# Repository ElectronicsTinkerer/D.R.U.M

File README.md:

# D.R.U.M (Digital Rhythmic Utility Modules)
Files for the D.R.U.M. Machine, the modular, expandable drum machine complete with digital AND analog circuitry!

## File Structure

```
.
├── doc             # Documentation on components, thoughts, h/sware details
├── module          # Files specific to the modules
│   ├── cad         # Housing design
│   ├── hardware    # PCB design (kicad)
│   └── software    # Module firmware
├── README.md       # INFO (this doc)
├── samples         # Sample to c-array conversion utils
│   └── bass-0      # Revision 0 Bass Drum samples (RAW, PCM-16)
├── sequencer       # Files specific to the sequencer
│   ├── cad         # Housing design
│   ├── hardware    # PCB design (kicad)
│   └── software    # Sequencer firmware
└── slidepot        # Slide potentiometer daughter board
    ├── cad         # 3D models for slidepot (knob)
    └── hardware    # Daughter board design
```

## System Architecture

The D.R.U.M. system is composed of a sequencer (the base and primary controller) and between 1 and 8 "modules." The digital section of each device is based on the RP2040 microcontroller, the same device found on the Raspberry Pi Pico development board. The RP2040 was selected due to its relatively high clock speed (compared to a '328, for example), multiple cores, its PIO state machines, good documentation, and great SDK. (Oh, and it's only $1). 

The **analog section** is designed around a completely passive routing scheme, where each of the channels is simply shifted one position over each module. This allows for up to 8 modules to be connected in series before a summing module is necessary to combine the channels. Each module has a 100k pull down resistor on the lines to ensure that they are not floating. The eight lines enter the sequencer for final summation and are dc isolated via separate capacitors for each line. Although currently unused, each module also has a comparator circuit on channel 8 to detect when all the channels have been filled to signal to the RP2040 onboard that the max channel count has been reached. Each module is in charge of the amplitude that it outputs; that is, the mixing between each module is performed on a per-module basis.

The **digital section** is designed around the RP2040 microcontroller. All the modules communicate over a 32-bit SPI-like scan chain which is controlled by the sequencer. The scan chain is further documented below. The modules have the ability to send an interrupt to the sequencer when they have been "(un)selected" by the user. Only one device can be "selected" at a time. Being selected means that that module's data will be copied to the sequencer and displayed on the UI. Deselection of the module hides this information from the user but retains it within the module's memory, allowing multiple modules to have different user data. Tempo synchronization between the modules is accomplished by an interrupt line which is driven by the sequencer. This outputs a periodic pulse each "tick" (currently each beat, but in the future when microbeats are implemented, this will pulse each microbeat). The length of the tick tells the module if the beat is the start of a new measure. A short pulse (<75us) is beat 0 while a long pulse (>75us) is any other beat.

The overall routing of signals is approximated by the following diagram:

## Docs

The `doc` directory contains most of the relevant documentation to this project. This will contain information about different parts of the system, such as the serial bus protocol or the data sheets for the components used.

* [`serbus.md`](doc/serbus.md) contains information on the custom 32-bit scan chain protocol used for communication between modules. This is implemented using the RP2040's PIO state machines, meaning that the bus can be much faster than bit-banging in software. It also allows an "address-free" control scheme, where modules (bus devices) are selected by their depth on the scan chain, rather than an address. This allows a user to completely fill the bus with 8 of the same module if desired.
* [`ipc.md`](doc/ipc.md) contains information on how information is sent between the different processes running on the sequencer and the module. Both CPU cores on the RP2040 are utilized in each design to allow simultaneous execution of multiple tasks. In the case of the sequencer, the I2C bus is rather slow compared to the amount of data to be sent over it, so the second thread (core 1) handles data modification and transfer to/from the modules.
* [`samples.md`](doc/samples.md) contains information on the used sample format and how playback is achieved as well as how the signed to unsigned conversion is performed.

## Usage

### Power Up / Reset

Upon power up, the sequencer will run through an auto detection routine to determine how many modules are connected. It also will cycle all neo pixels in the 4x4 grid pad white to visually test that all LEDs and their individual colors are functioning properly. After this initialization sequence is performed, the sequencer will display its default config on the OLED screen.

### Programming a Beat

To start programming in a beat, the user must first select the module that they would like to program. Modules should have a button on board along with a visual indicator which can be used to select/deselect a module and identify if a module is selected. When a module is selected, the current contents of the sequencer's beat grid are saved to the previously selected module and the newly selected module's saved beat data is loaded into the grid.

Each square on the grid represents a sixteenth note (1/16) at the current tempo marking (although this may be changed in future revisions). Additionally, each square can have up to 7 different values associated with it. These values are called the *velocity* of that note. In addition to the 7 different velocities, a square can be off, giving 8 total possible states. The state of all the squares is indicated by the color of that square. Additionally, each time that a square is pressed, its new velocity value is displayed on the OLED screen to give quantitative feedback on any changes. Beats can be programmed while the sequencer is in active playback or while the system is in a stopped state.

### Playback

Playback is controlled by the tempo knob. This knob controls the tempo by rotating it; clockwise increases the tempo by one beat per minute per click of the knob and counter-clockwise decreases the tempo. Pressing the know will switch the sequencer between active playback, *sequencing*, and stopped, *idle*, states. During playback, the current square will light up white to indicate the location of the beat. This light will extinguish during the idle state.

The time signature of the playback can be changed via the time signature knob. This cycles through all built-in time signatures in a circular manner. Beats which are not available in a given time signature will be "grayed out" with a dim white square. Note that beats which had been programmed before changing the time signature but are not available in a new time signature will retain their original values but will not be played back. Holding down the time signature knob for about one second will clear the current pattern on the grid.

### Interface

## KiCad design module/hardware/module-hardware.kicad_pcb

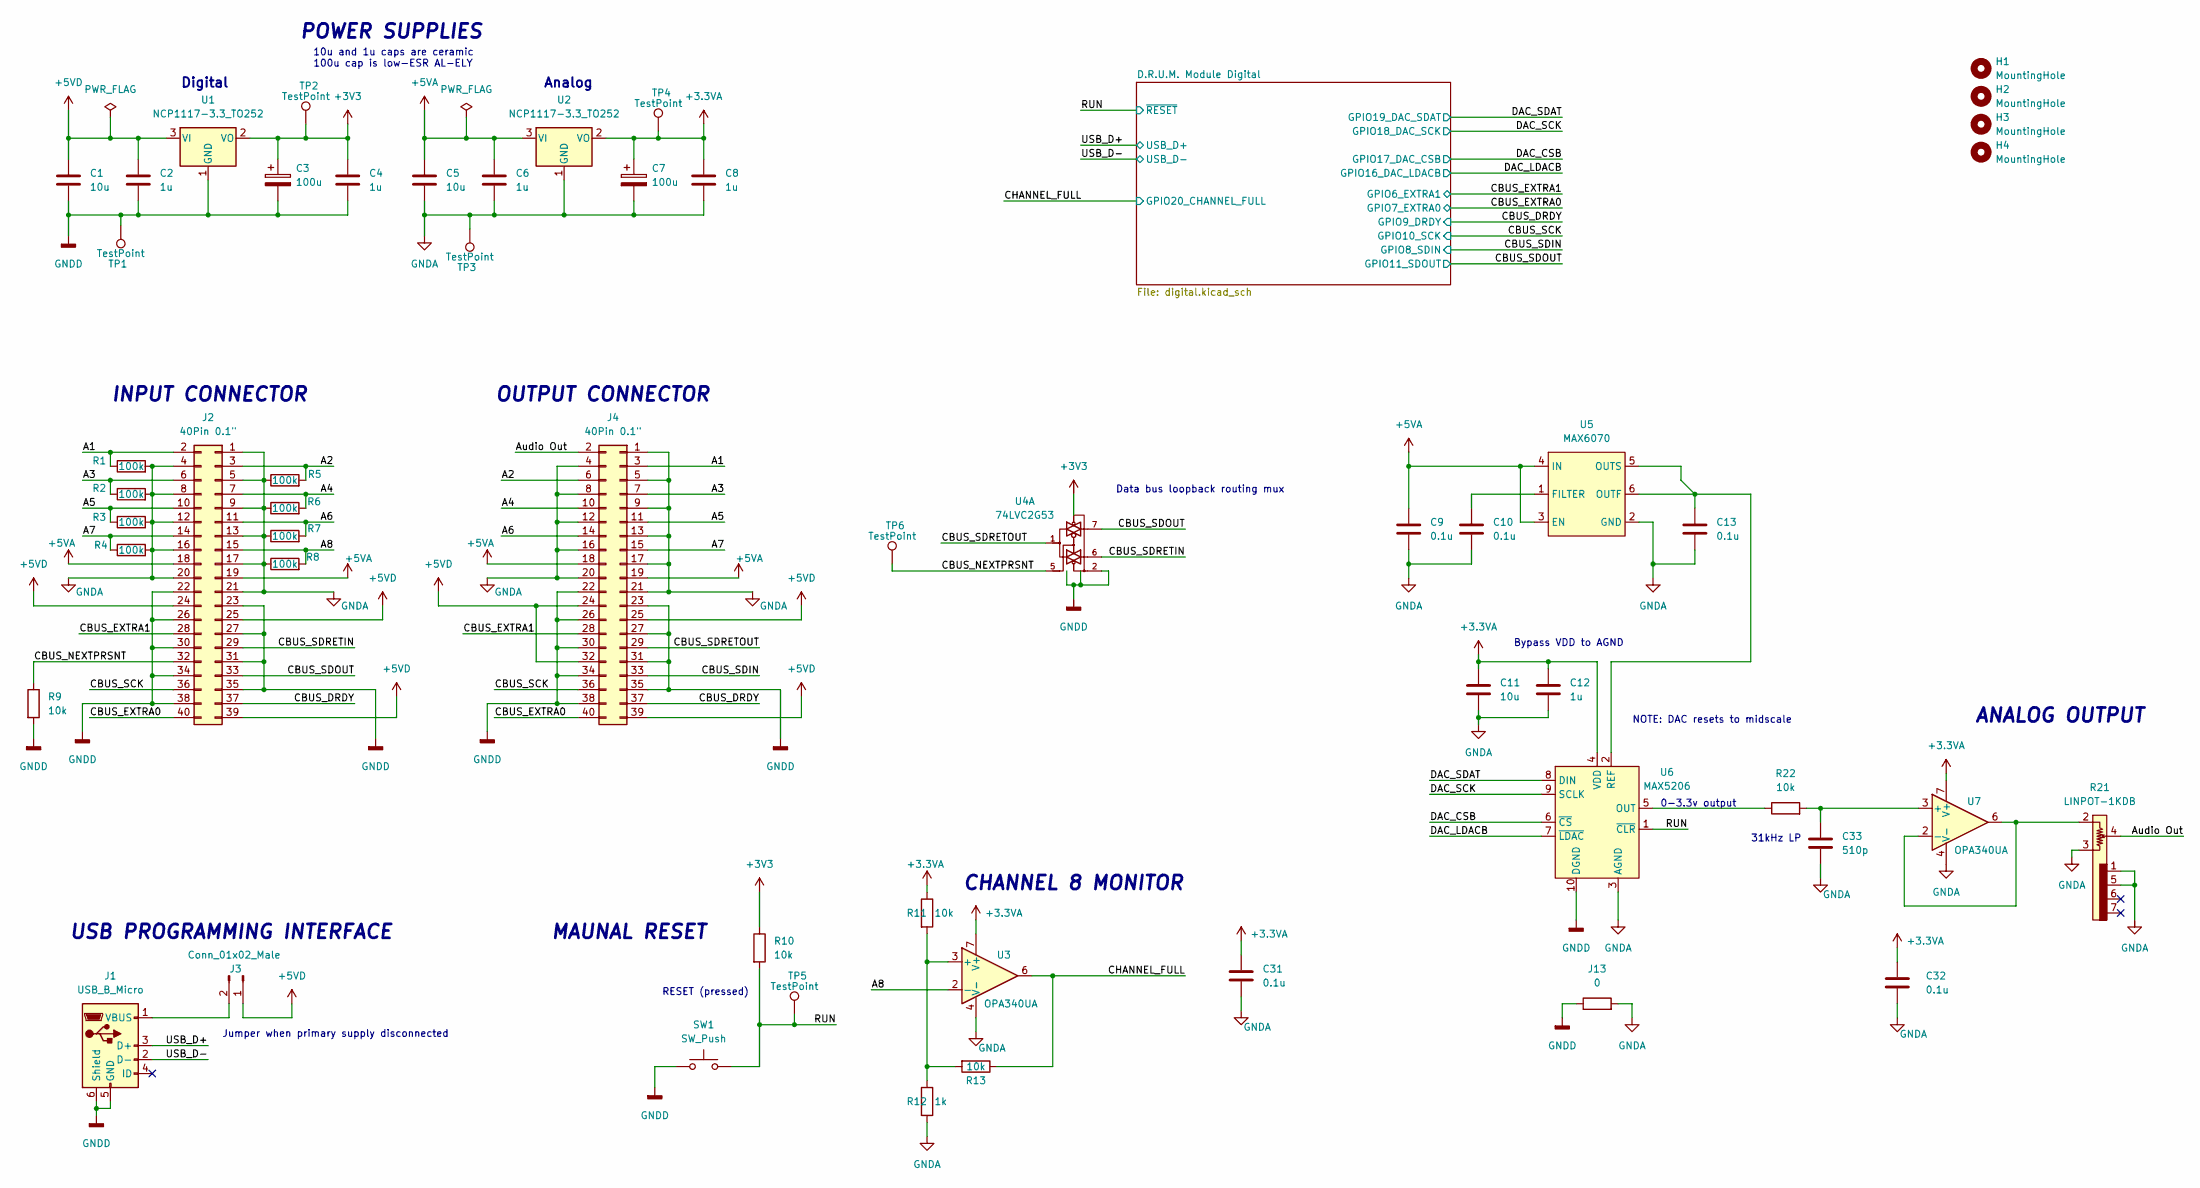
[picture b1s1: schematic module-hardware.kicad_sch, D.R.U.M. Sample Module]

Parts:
C1, C5, C11: 10u; C_1206_3216Metric_Pad1.33x1.80mm_HandSolder
C2, C4, C6, C8, C12: 1u; C_0603_1608Metric_Pad1.08x0.95mm_HandSolder
C3, C7: 100u; CP_Radial_D8.0mm_P3.50mm
C9, C10, C13, C31, C32: 0.1u; C_0603_1608Metric_Pad1.08x0.95mm_HandSolder
C33: 510p; C_0603_1608Metric_Pad1.08x0.95mm_HandSolder
H1, H2, H3, H4: MountingHole; MountingHole_3.2mm_M3
J1: USB_B_Micro; USB_Micro-B_Amphenol_10104110_Horizontal
J2: 40Pin 0.1"; PinHeader_2x20_P2.54mm_Horizontal
J3: Conn_01x02_Male; PinHeader_1x02_P2.54mm_Vertical
J4: 40Pin 0.1"; PinSocket_2x20_P2.54mm_Horizontal
J13: 0; SolderJumper-2_P1.3mm_Open_TrianglePad1.0x1.5mm
R1, R2, R3, R4, R5, R6, R7, R8: 100k; R_1206_3216Metric_Pad1.30x1.75mm_HandSolder
R9, R10, R11, R13, R22: 10k; R_0603_1608Metric_Pad0.98x0.95mm_HandSolder
R12: 1k; R_0603_1608Metric_Pad0.98x0.95mm_HandSolder
R21: LINPOT-1KDB; LINPOT-10KDB
SW1: SW_Push; TE_ConnMSLPT5252CG1
TP1, TP2, TP3, TP4, TP5, TP6: TestPoint; TestPoint_Pad_D1.5mm
U1, U2: NCP1117-3.3_TO252; TO-252-2
U3, U7: OPA340UA; SOIC-8_3.9x4.9mm_P1.27mm
U4: 74LVC2G53; VSSOP-8_2.3x2mm_P0.5mm
U5: MAX6070; SOT-23-6_Handsoldering
U6: MAX5206; MSOP-10_3x3mm_P0.5mm

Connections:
+3.3VA: C7.1, C8.1, C11.1, C12.1, C31.1, C32.1, R11.1, TP4.1, U2.2 (VO), U3.7 (V+), U6.4 (VDD), U7.7 (V+)
+3V3: C3.1, C4.1, R10.1, TP2.1, U1.2 (VO), U4.8 (VCC); also elsewhere on the board
+5VA: C5.1, C6.1, C9.1, J2.18, J2.19, J4.18, J4.19, U2.3 (VI), U5.3 (EN), U5.4 (IN)
+5VD: C1.1, C2.1, J2.24, J2.25, J2.39, J3.1, J4.24, J4.25, J4.32, J4.39, U1.3 (VI)
/A1: J2.2, J4.3, R1.1
/A2: J2.3, J4.6, R5.2
/A3: J2.6, J4.7, R2.1
/A4: J2.7, J4.10, R6.2
/A5: J2.10, J4.11, R3.1
/A6: J2.11, J4.14, R7.2
/A7: J2.14, J4.15, R4.1
/A8: J2.15, R8.2, U3.2 (-)
/Audio Out: J4.2, R21.4
/CBUS_DRDY: J2.37, J4.37; also elsewhere on the board
/CBUS_EXTRA0: J2.40, J4.40; also elsewhere on the board
/CBUS_EXTRA1: J2.28, J4.28; also elsewhere on the board
/CBUS_NEXTPRSNT: J2.32, R9.1, TP6.1, U4.5
/CBUS_SCK: J2.36, J4.36; also elsewhere on the board
/CBUS_SDIN: J4.33; also elsewhere on the board
/CBUS_SDOUT: J2.33, U4.7; also elsewhere on the board
/CBUS_SDRETIN: J2.29, U4.6
/CBUS_SDRETOUT: J4.29, U4.1
/CHANNEL_FULL: R13.1, U3.6; also elsewhere on the board
/DAC_CSB: U6.6 (~CS); also elsewhere on the board
/DAC_LDACB: U6.7 (~LDAC); also elsewhere on the board
/DAC_SCK: U6.9 (SCLK); also elsewhere on the board
/DAC_SDAT: U6.8 (DIN); also elsewhere on the board
/RUN: R10.2, SW1.2, TP5.1, U6.1 (~CLR); also elsewhere on the board
/USB_D+: J1.3 (D+); also elsewhere on the board
/USB_D-: J1.2 (D-); also elsewhere on the board
GND: C1.2, C2.2, C3.2, C4.2, J1.5 (GND), J1.6 (Shield), J2.22, J2.23, J2.26, J2.27, J2.30, J2.31, J2.34, J2.35, J2.38, J4.22, J4.23, J4.26, J4.27, J4.30, J4.31, J4.34, J4.35, J4.38, J13.1, R9.2, SW1.1, TP1.1, U1.1 (GND), U4.2, U4.3 (GND), U4.4 (GND), U6.10 (DGND); also elsewhere on the board
GNDA: C5.2, C6.2, C7.2, C8.2, C9.2, C10.2, C11.2, C12.2, C13.2, C31.2, C32.2, C33.2, J2.1, J2.4, J2.5, J2.8, J2.9, J2.12, J2.13, J2.16, J2.17, J2.20, J2.21, J4.1, J4.4, J4.5, J4.8, J4.9, J4.12, J4.13, J4.16, J4.17, J4.20, J4.21, J13.2, R1.2, R2.2, R3.2, R4.2, R5.1, R6.1, R7.1, R8.1, R12.2, R21.1, R21.3, R21.5, TP3.1, U2.1 (GND), U3.4 (V-), U5.2 (GND), U6.3 (AGND), U7.4 (V-)
unnamed: C10.1, U5.1 (FILTER)
unnamed: C13.1, U5.5 (OUTS), U5.6 (OUTF), U6.2 (REF)
unnamed: C33.1, R22.2, U7.3 (+)
unnamed: J1.1 (VBUS), J3.2
unnamed: R11.2, R12.1, R13.2, U3.3 (+)
unnamed: R21.2, U7.2 (-), U7.6
unnamed: R22.1, U6.5 (OUT)

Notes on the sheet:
USB PROGRAMMING INTERFACE
Analog
ANALOG OUTPUT
10u and 1u caps are ceramic 100u cap is low-ESR AL-ELY
Data bus loopback routing mux
Jumper when primary supply disconnected
MAUNAL RESET
CHANNEL 8 MONITOR
0-3.3v output
POWER SUPPLIES
Bypass VDD to AGND
NOTE: DAC resets to midscale
RESET (pressed)
INPUT CONNECTOR
OUTPUT CONNECTOR
31kHz LP
Digital

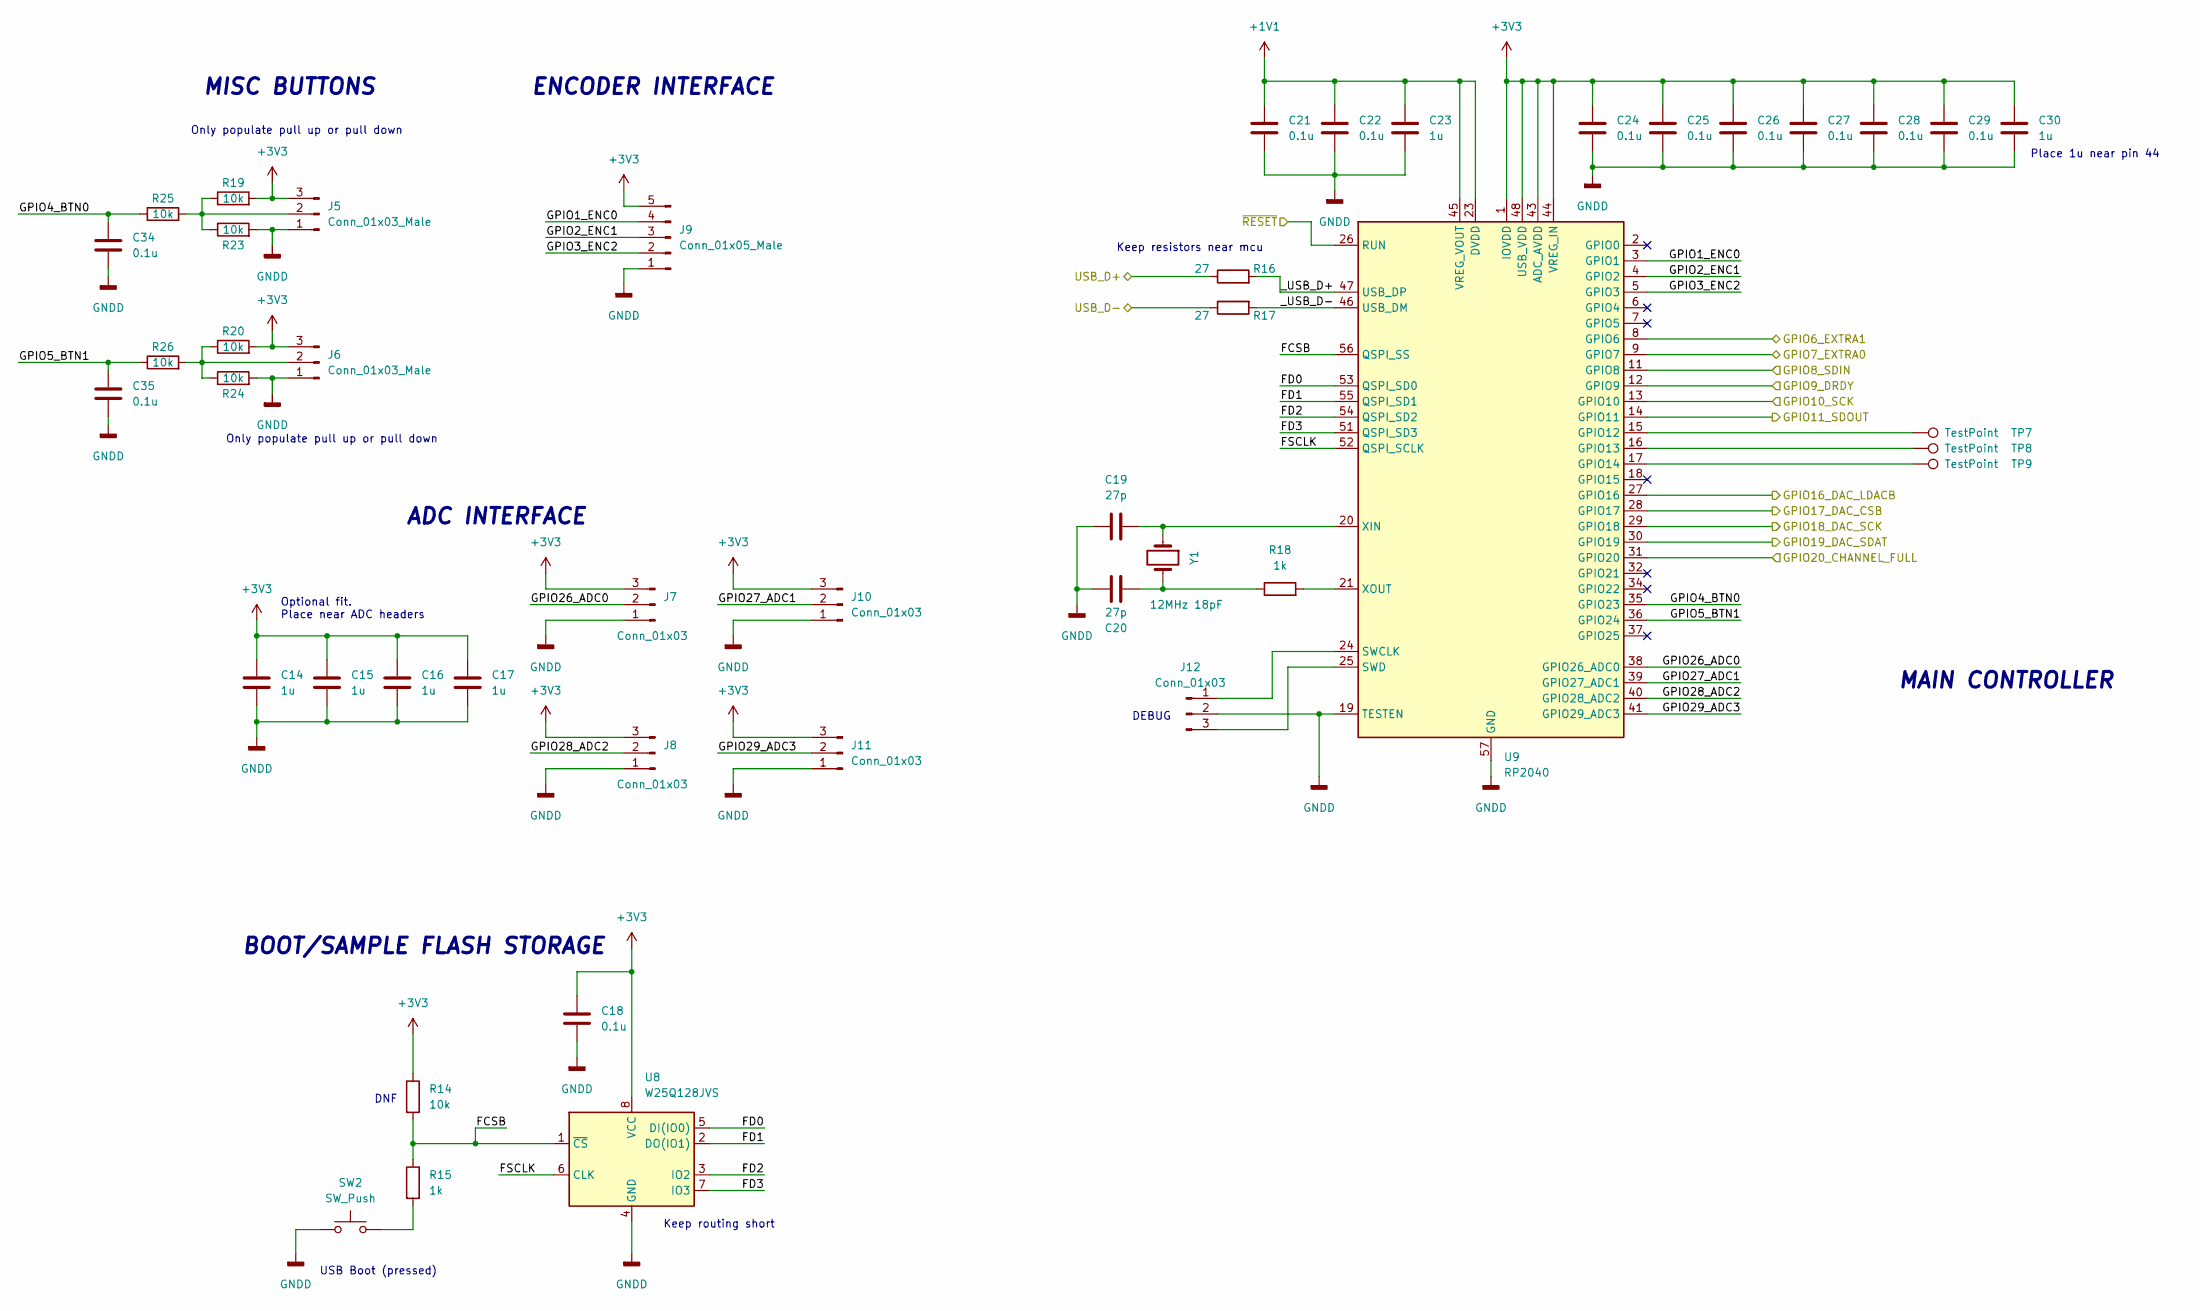
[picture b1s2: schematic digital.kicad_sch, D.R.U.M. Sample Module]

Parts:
C14, C15, C16, C17, C23, C30: 1u; C_0603_1608Metric_Pad1.08x0.95mm_HandSolder
C18, C21, C22, C24, C25, C26, C27, C28, C29, C34, C35: 0.1u; C_0603_1608Metric_Pad1.08x0.95mm_HandSolder
C19, C20: 27p; C_0603_1608Metric_Pad1.08x0.95mm_HandSolder
J5, J6: Conn_01x03_Male; PinHeader_1x03_P2.54mm_Vertical
J7, J8, J10, J11, J12: Conn_01x03; PinHeader_1x03_P2.54mm_Vertical
J9: Conn_01x05_Male; PinHeader_1x05_P2.54mm_Vertical
R14, R19, R20, R23, R24, R25, R26: 10k; R_0603_1608Metric_Pad0.98x0.95mm_HandSolder
R15, R18: 1k; R_0603_1608Metric_Pad0.98x0.95mm_HandSolder
R16, R17: 27; R_0603_1608Metric_Pad0.98x0.95mm_HandSolder
SW2: SW_Push; TE_ConnMSLPT5252CG1
TP7, TP8, TP9: TestPoint; TestPoint_Pad_D1.5mm
U8: W25Q128JVS; SOIC-8_5.23x5.23mm_P1.27mm
U9: RP2040; QFN-56-1EP_7x7mm_P0.4mm_EP3.2x3.2mm
Y1: 12MHz 18pF; Crystal_SMD_HC49-SD

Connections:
+1V1: C21.1, C22.1, C23.1, U9.23 (DVDD), U9.45 (VREG_VOUT), U9.50 (DVDD)
+3V3: C14.1, C15.1, C16.1, C17.1, C18.1, C24.1, C25.1, C26.1, C27.1, C28.1, C29.1, C30.1, J5.3, J6.3, J7.3, J8.3, J9.5, J10.3, J11.3, R14.1, R19.2, R20.2, U8.8 (VCC), U9.1 (IOVDD), U9.10 (IOVDD), U9.22 (IOVDD), U9.33 (IOVDD), U9.42 (IOVDD), U9.43 (ADC_AVDD), U9.44 (VREG_IN), U9.48 (USB_VDD), U9.49 (IOVDD); also elsewhere on the board
/CBUS_DRDY: U9.12 (GPIO9); also elsewhere on the board
/CBUS_EXTRA0: U9.9 (GPIO7); also elsewhere on the board
/CBUS_EXTRA1: U9.8 (GPIO6); also elsewhere on the board
/CBUS_SCK: U9.13 (GPIO10); also elsewhere on the board
/CBUS_SDIN: U9.11 (GPIO8); also elsewhere on the board
/CBUS_SDOUT: U9.14 (GPIO11); also elsewhere on the board
/CHANNEL_FULL: U9.31 (GPIO20); also elsewhere on the board
/D.R.U.M. Module Digital/FCSB: R14.2, R15.1, U8.1 (~CS), U9.56 (QSPI_SS)
/D.R.U.M. Module Digital/FD0: U8.5 (DI(IO0)), U9.53 (QSPI_SD0)
/D.R.U.M. Module Digital/FD1: U8.2 (DO(IO1)), U9.55 (QSPI_SD1)
/D.R.U.M. Module Digital/FD2: U8.3 (IO2), U9.54 (QSPI_SD2)
/D.R.U.M. Module Digital/FD3: U8.7 (IO3), U9.51 (QSPI_SD3)
/D.R.U.M. Module Digital/FSCLK: U8.6 (CLK), U9.52 (QSPI_SCLK)
/D.R.U.M. Module Digital/GPIO1_ENC0: J9.4, U9.3 (GPIO1)
/D.R.U.M. Module Digital/GPIO2_ENC1: J9.3, U9.4 (GPIO2)
/D.R.U.M. Module Digital/GPIO3_ENC2: J9.2, U9.5 (GPIO3)
/D.R.U.M. Module Digital/GPIO4_BTN0: C34.1, R25.1, U9.35 (GPIO23)
/D.R.U.M. Module Digital/GPIO5_BTN1: C35.1, R26.1, U9.36 (GPIO24)
/D.R.U.M. Module Digital/GPIO26_ADC0: J7.2, U9.38 (GPIO26_ADC0)
/D.R.U.M. Module Digital/GPIO27_ADC1: J10.2, U9.39 (GPIO27_ADC1)
/D.R.U.M. Module Digital/GPIO28_ADC2: J8.2, U9.40 (GPIO28_ADC2)
/D.R.U.M. Module Digital/GPIO29_ADC3: J11.2, U9.41 (GPIO29_ADC3)
/D.R.U.M. Module Digital/_USB_D+: R16.2, U9.47 (USB_DP)
/D.R.U.M. Module Digital/_USB_D-: R17.2, U9.46 (USB_DM)
/DAC_CSB: U9.28 (GPIO17); also elsewhere on the board
/DAC_LDACB: U9.27 (GPIO16); also elsewhere on the board
/DAC_SCK: U9.29 (GPIO18); also elsewhere on the board
/DAC_SDAT: U9.30 (GPIO19); also elsewhere on the board
/RUN: U9.26 (RUN); also elsewhere on the board
/USB_D+: R16.1; also elsewhere on the board
/USB_D-: R17.1; also elsewhere on the board
GND: C14.2, C15.2, C16.2, C17.2, C18.2, C19.1, C20.2, C21.2, C22.2, C23.2, C24.2, C25.2, C26.2, C27.2, C28.2, C29.2, C30.2, C34.2, C35.2, J5.1, J6.1, J7.1, J8.1, J9.1, J10.1, J11.1, J12.2, R23.2, R24.2, SW2.1, U8.4 (GND), U9.19 (TESTEN), U9.57 (GND); also elsewhere on the board
unnamed: C19.2, U9.20 (XIN), Y1.1
unnamed: C20.1, R18.1, Y1.2
unnamed: J5.2, R19.1, R23.1, R25.2
unnamed: J6.2, R20.1, R24.1, R26.2
unnamed: J12.1, U9.24 (SWCLK)
unnamed: J12.3, U9.25 (SWD)
unnamed: R15.2, SW2.2
unnamed: R18.2, U9.21 (XOUT)
unnamed: TP7.1, U9.15 (GPIO12)
unnamed: TP8.1, U9.16 (GPIO13)
unnamed: TP9.1, U9.17 (GPIO14)

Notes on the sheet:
Only populate pull up or pull down
Optional fit. Place near ADC headers
DEBUG
Keep resistors near mcu
USB Boot (pressed)
MAIN CONTROLLER
MISC BUTTONS
DNF
ENCODER INTERFACE
Keep routing short
Place 1u near pin 44
BOOT/SAMPLE FLASH STORAGE
ADC INTERFACE

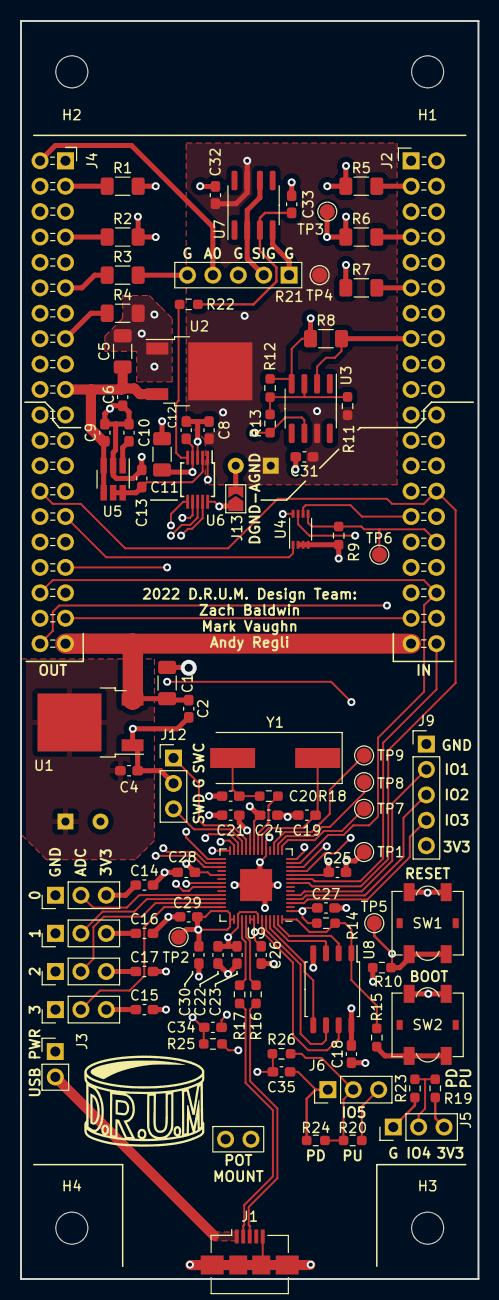
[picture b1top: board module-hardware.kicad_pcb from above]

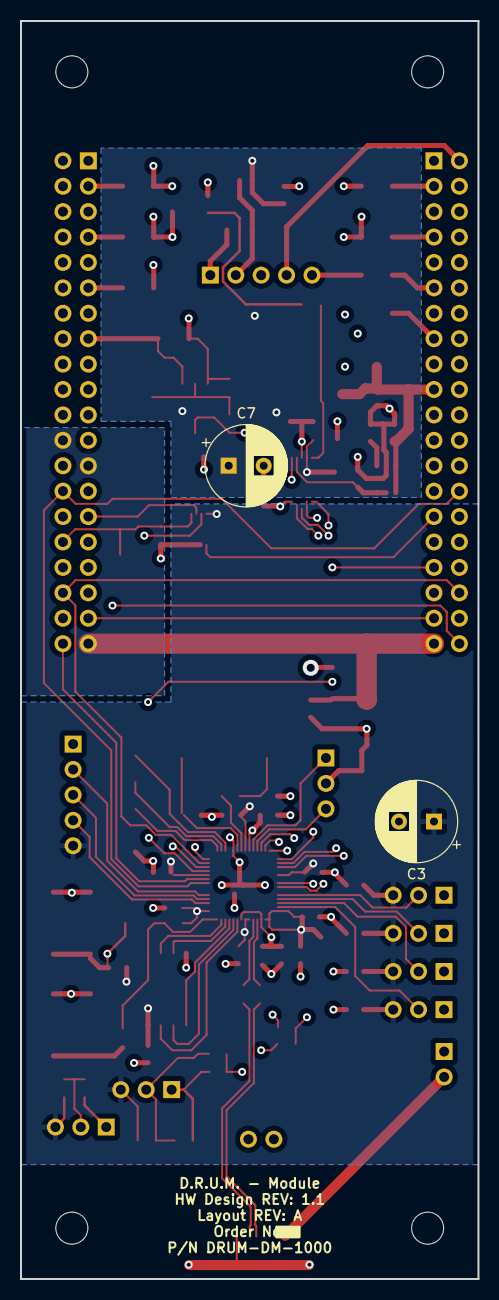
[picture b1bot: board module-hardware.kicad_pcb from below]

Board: 4 copper layers, 45.7 x 125.7 mm, 99 parts (2 on the bottom side), 68 nets.

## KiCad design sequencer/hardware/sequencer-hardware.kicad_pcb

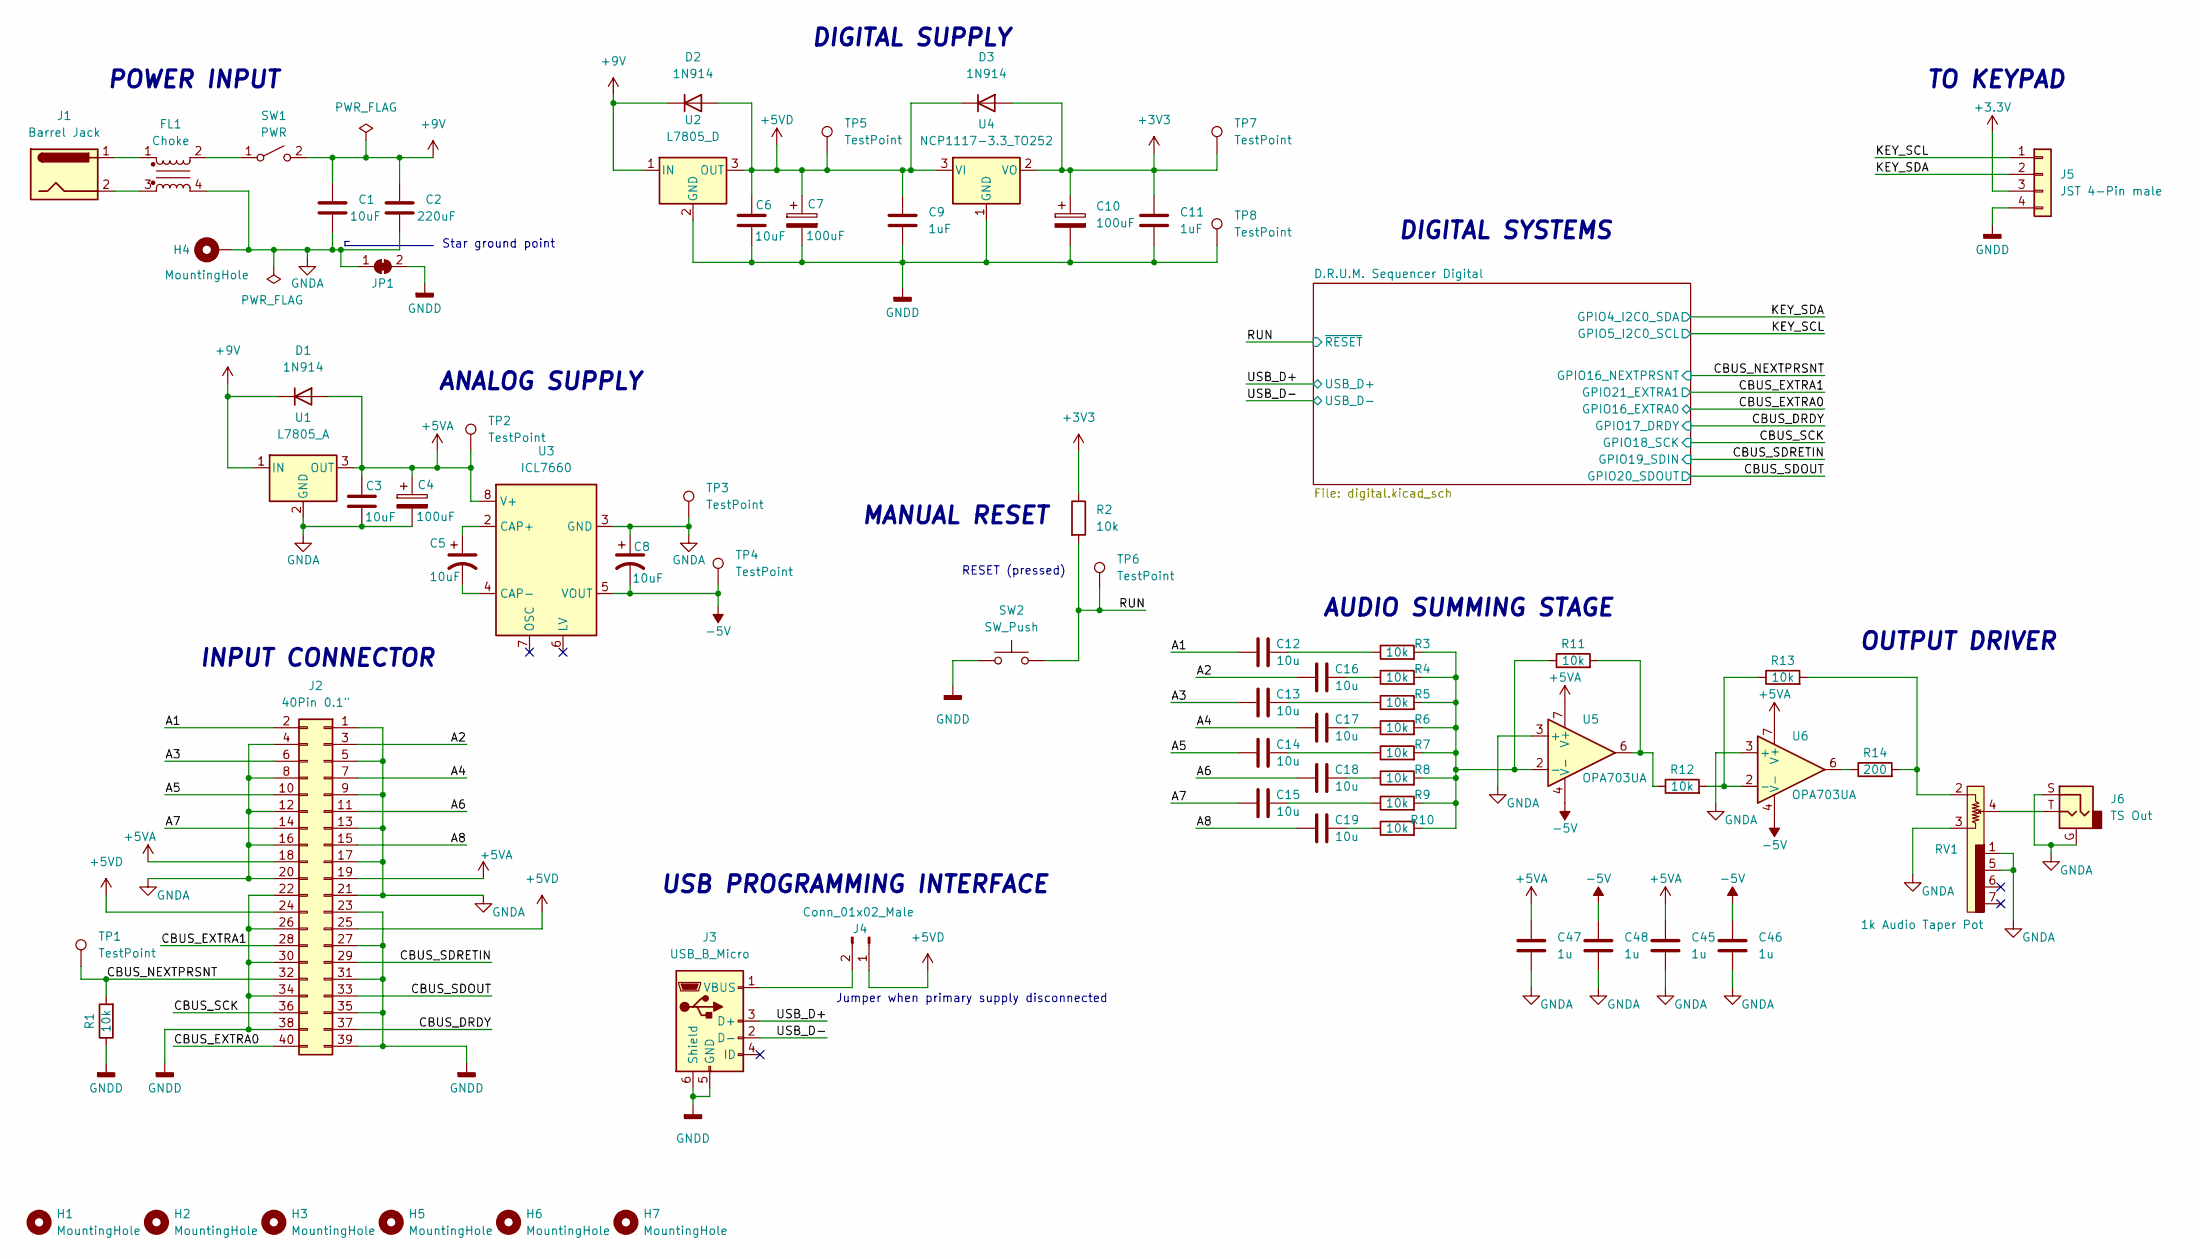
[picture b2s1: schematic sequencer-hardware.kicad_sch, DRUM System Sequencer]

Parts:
C1, C3, C5, C6, C8: 10uF; C_1206_3216Metric_Pad1.33x1.80mm_HandSolder
C2: 220uF; CP_Radial_D8.0mm_P3.50mm
C4, C7, C10: 100uF; CP_Radial_D8.0mm_P3.50mm
C9, C11: 1uF; C_0603_1608Metric_Pad1.08x0.95mm_HandSolder
C12, C13, C14, C15, C16, C17, C18, C19: 10u; C_1206_3216Metric_Pad1.33x1.80mm_HandSolder
C45, C46, C47, C48: 1u; C_0603_1608Metric_Pad1.08x0.95mm_HandSolder
D1, D2, D3: 1N914; D_DO-35_SOD27_P7.62mm_Horizontal
FL1: Choke; Choke_Schaffner_RN102-04-14.0x14.0mm
H1, H2, H3, H5, H6, H7: MountingHole; MountingHole_3.2mm_M3_ISO14580
H4: MountingHole; MountingHole_3.2mm_M3_ISO14580_Pad
J1: Barrel Jack; BarrelJack_Horizontal
J2: 40Pin 0.1"; PinHeader_2x20_P2.54mm_Horizontal
J3: USB_B_Micro; USB_Micro-B_Amphenol_10104110_Horizontal
J4: Conn_01x02_Male; PinHeader_1x02_P2.54mm_Vertical
J5: JST 4-Pin male; JST_PH_B4B-PH-K_1x04_P2.00mm_Vertical
J6: TS Out; Jack_6.35mm_Neutrik_NRJ6HF-AU_Horizontal
JP1: SolderJumper_2_Bridged; SolderJumper-2_P1.3mm_Bridged_Pad1.0x1.5mm
R1, R2, R3, R4, R5, R6, R7, R8, R9, R10, R11, R12, R13: 10k; R_0603_1608Metric_Pad0.98x0.95mm_HandSolder
R14: 200; R_0603_1608Metric_Pad0.98x0.95mm_HandSolder
RV1: 1k Audio Taper Pot; LINPOT-10KDB
SW1: PWR; PinHeader_1x02_P2.00mm_Vertical
SW2: SW_Push; TE_ConnMSLPT5252CG1
TP1, TP2, TP3, TP4, TP5, TP6, TP7, TP8: TestPoint; TestPoint_Pad_D1.5mm
U1: L7805_A; TO-220-3_Horizontal_TabDown
U2: L7805_D; TO-220-3_Horizontal_TabDown
U3: ICL7660; SOIC-8_3.9x4.9mm_P1.27mm
U4: NCP1117-3.3_TO252; TO-252-2
U5, U6: OPA703UA; SOIC-8_3.9x4.9mm_P1.27mm

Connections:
+5VA: C3.1, C4.1, C45.1, C47.1, D1.2 (A), J2.18, J2.19, TP2.1, U1.3 (OUT), U3.8 (V+), U5.7 (V+), U6.7 (V+)
+5VD: C6.1, C7.1, C9.1, D2.2 (A), D3.1 (K), J2.24, J2.25, J4.1, TP5.1, U2.3 (OUT), U4.3 (VI)
+9V: C1.1, C2.1, D1.1 (K), D2.1 (K), SW1.2 (B), U1.1 (IN), U2.1 (IN)
-5V: C8.2, C46.1, C48.1, TP4.1, U3.5 (VOUT), U5.4 (V-), U6.4 (V-)
/A1: C12.1, J2.2
/A2: C16.1, J2.3
/A3: C13.1, J2.6
/A4: C17.1, J2.7
/A5: C14.1, J2.10
/A6: C18.1, J2.11
/A7: C15.1, J2.14
/A8: C19.1, J2.15
/CBUS_DRDY: J2.37; also elsewhere on the board
/CBUS_EXTRA0: J2.40; also elsewhere on the board
/CBUS_EXTRA1: J2.28; also elsewhere on the board
/CBUS_NEXTPRSNT: J2.32, R1.2, TP1.1; also elsewhere on the board
/CBUS_SCK: J2.36; also elsewhere on the board
/CBUS_SDOUT: J2.33; also elsewhere on the board
/CBUS_SDRETIN: J2.29; also elsewhere on the board
/KEY_SCL: J5.1; also elsewhere on the board
/KEY_SDA: J5.2; also elsewhere on the board
/RUN: R2.2, SW2.2, TP6.1; also elsewhere on the board
/USB_D+: J3.3 (D+); also elsewhere on the board
/USB_D-: J3.2 (D-); also elsewhere on the board
GNDA: C1.2, C2.2, C3.2, C4.2, C8.1, C45.2, C46.2, C47.2, C48.2, FL1.4, H4.1, J2.1, J2.4, J2.5, J2.8, J2.9, J2.12, J2.13, J2.16, J2.17, J2.20, J2.21, J6.G, J6.S, JP1.1 (A), RV1.1, RV1.3, RV1.5, TP3.1, U1.2 (GND), U3.3 (GND), U5.3 (+), U6.3 (+)
GNDD: C6.2, C7.2, C9.2, C10.2, C11.2, J2.22, J2.23, J2.26, J2.27, J2.30, J2.31, J2.34, J2.35, J2.38, J2.39, J3.5 (GND), J3.6 (Shield), J5.4, JP1.2 (B), R1.1, SW2.1, TP8.1, U2.2 (GND), U4.1 (GND); also elsewhere on the board
unnamed: C5.1, U3.2 (CAP+)
unnamed: C5.2, U3.4 (CAP-)
unnamed: C12.2, R3.1
unnamed: C13.2, R5.1
unnamed: C14.2, R7.1
unnamed: C15.2, R9.1
unnamed: C16.2, R4.1
unnamed: C17.2, R6.1
unnamed: C18.2, R8.1
unnamed: C19.2, R10.1
unnamed: FL1.1, J1.1
unnamed: FL1.2, SW1.1 (A)
unnamed: FL1.3, J1.2
unnamed: J3.1 (VBUS), J4.2
unnamed: J6.T, RV1.4
unnamed: R3.2, R4.2, R5.2, R6.2, R7.2, R8.2, R9.2, R10.2, R11.1, U5.2 (-)
unnamed: R11.2, R12.1, U5.6
unnamed: R12.2, R13.1, U6.2 (-)
unnamed: R13.2, R14.2, RV1.2
unnamed: R14.1, U6.6

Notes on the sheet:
OUTPUT DRIVER
Jumper when primary supply disconnected
TO KEYPAD
RESET (pressed)
MANUAL RESET
INPUT CONNECTOR
DIGITAL SYSTEMS
DIGITAL SUPPLY
USB PROGRAMMING INTERFACE
AUDIO SUMMING STAGE
ANALOG SUPPLY
POWER INPUT
Star ground point
